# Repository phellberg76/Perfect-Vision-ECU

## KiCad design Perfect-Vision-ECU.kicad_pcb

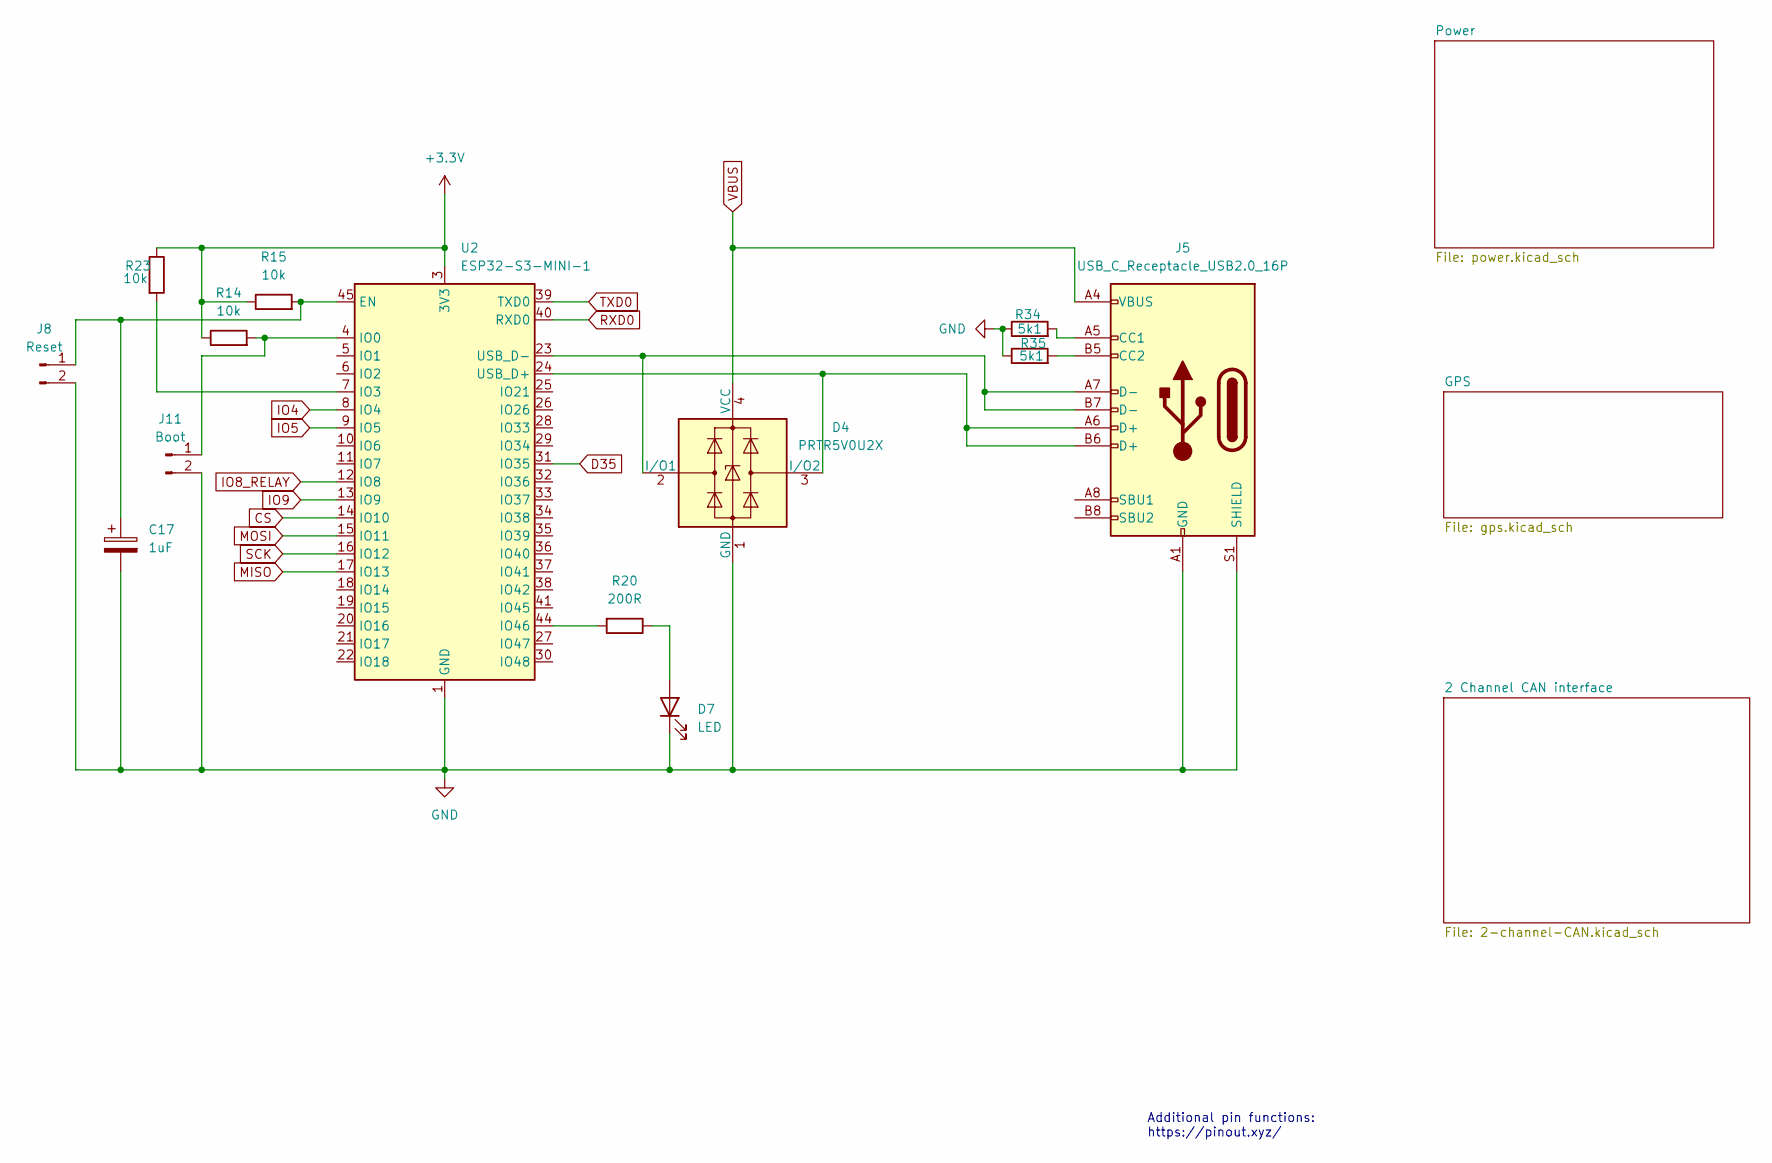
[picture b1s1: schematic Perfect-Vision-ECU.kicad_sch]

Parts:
C17: 1uF; C_0402_1005Metric
D4: PRTR5V0U2X; SOT-143
D7: LED; LED_0603_1608Metric
J5: USB_C_Receptacle_USB2.0_16P; USB_C_Receptacle_HRO_TYPE-C-31-M-12
J8: Reset; PinHeader_1x02_P2.54mm_Vertical
J11: Boot; PinHeader_1x02_P2.54mm_Vertical
R14, R15, R23: 10k; R_0402_1005Metric
R20: 200R; R_0603_1608Metric
R34, R35: 5k1; R_0402_1005Metric
U2: ESP32-S3-MINI-1; ESP32-S2-MINI-1

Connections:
+3.3V: R14.1, R15.1, R23.1, U2.3 (3V3); also elsewhere on the board
CS: U2.14 (IO10); also elsewhere on the board
D35: U2.31 (IO35); also elsewhere on the board
GND: C17.2, D4.1 (GND), D7.1 (K), J5.A1 (GND), J5.A12 (GND), J5.B1 (GND), J5.B12 (GND), J5.S1 (SHIELD), J8.2, J11.2, R34.1, R35.1, U2.1 (GND), U2.2 (GND), U2.42 (GND), U2.43 (GND), U2.46 (GND), U2.47 (GND), U2.48 (GND), U2.49 (GND), U2.50 (GND), U2.51 (GND), U2.52 (GND), U2.53 (GND), U2.54 (GND), U2.55 (GND), U2.56 (GND), U2.57 (GND), U2.58 (GND), U2.59 (GND), U2.60 (GND), U2.61 (GND), U2.62 (GND), U2.63 (GND), U2.64 (GND), U2.65 (GND); also elsewhere on the board
IO4: U2.8 (IO4); also elsewhere on the board
IO5: U2.9 (IO5); also elsewhere on the board
IO8_RELAY: U2.12 (IO8); also elsewhere on the board
IO9: U2.13 (IO9); also elsewhere on the board
MISO: U2.17 (IO13); also elsewhere on the board
MOSI: U2.15 (IO11); also elsewhere on the board
unnamed: D4.2 (I/O1), J5.A7 (D-), J5.B7 (D-), U2.23 (USB_D-)
unnamed: D4.3 (I/O2), J5.A6 (D+), J5.B6 (D+), U2.24 (USB_D+)
unnamed: D7.2 (A), R20.1
unnamed: J5.A5 (CC1), R34.2
unnamed: J5.B5 (CC2), R35.2
unnamed: C17.1, J8.1, R15.2, U2.45 (EN)
unnamed: J11.1, R14.2, U2.4 (IO0)
unnamed: R23.2, U2.7 (IO3)
unnamed: R20.2, U2.44 (IO46)
RXD0: U2.40 (RXD0); also elsewhere on the board
SCK: U2.16 (IO12); also elsewhere on the board
TXD0: U2.39 (TXD0); also elsewhere on the board
VBUS: D4.4 (VCC), J5.A4 (VBUS), J5.A9 (VBUS), J5.B4 (VBUS), J5.B9 (VBUS); also elsewhere on the board

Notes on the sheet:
Additional pin functions: https://pinout.xyz/

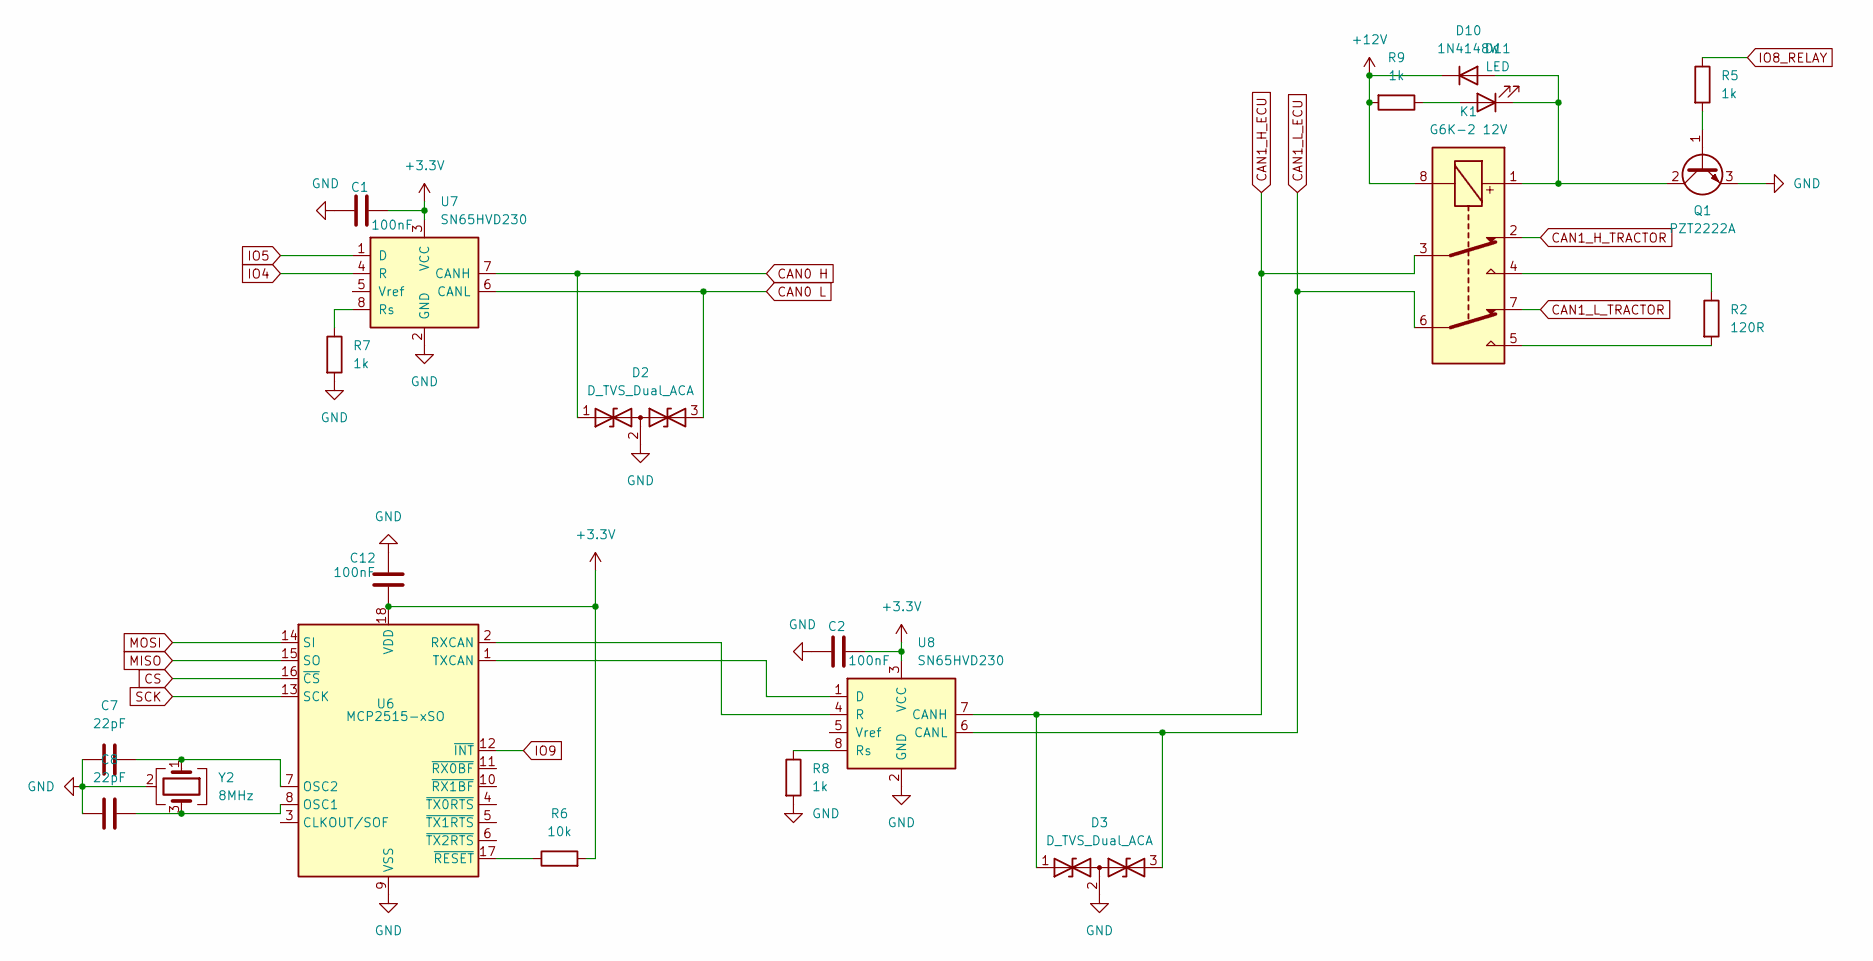
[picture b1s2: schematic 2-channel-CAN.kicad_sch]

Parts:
C1, C2, C12: 100nF; C_0402_1005Metric
C7, C8: 22pF; C_0402_1005Metric
D2, D3: D_TVS_Dual_ACA; SOT-23
D10: 1N4148W; D_SOD-123
D11: LED; LED_0603_1608Metric
K1: G6K-2 12V; Relay_DPDT_Omron_G6K-2F-Y
Q1: PZT2222A; SOT-223-3_TabPin2
R2: 120R; R_0402_1005Metric
R5, R7, R8, R9: 1k; R_0402_1005Metric
R6: 10k; R_0402_1005Metric
U6: MCP2515-xSO; SOIC-18W_7.5x11.6mm_P1.27mm
U7, U8: SN65HVD230; SOIC-8_3.9x4.9mm_P1.27mm
Y2: 8MHz; Crystal_SMD_3225-4Pin_3.2x2.5mm

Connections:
+3.3V: C1.1, C2.1, C12.2, R6.2, U6.18 (VDD), U7.3 (VCC), U8.3 (VCC); also elsewhere on the board
+12V: D10.1 (K), K1.8, R9.2; also elsewhere on the board
CAN0 H: D2.1 (A1), U7.7 (CANH); also elsewhere on the board
CAN0 L: D2.3 (A2), U7.6 (CANL); also elsewhere on the board
CAN1_H_ECU: D3.1 (A1), K1.3, U8.7 (CANH); also elsewhere on the board
CAN1_H_TRACTOR: K1.2; also elsewhere on the board
CAN1_L_ECU: D3.3 (A2), K1.6, U8.6 (CANL); also elsewhere on the board
CAN1_L_TRACTOR: K1.7; also elsewhere on the board
CS: U6.16 (~CS); also elsewhere on the board
GND: C1.2, C2.2, C7.1, C8.1, C12.1, D2.2 (common), D3.2 (common), Q1.3 (E), R7.2, R8.2, U6.9 (VSS), U7.2 (GND), U8.2 (GND), Y2.2 (G), Y2.4 (G); also elsewhere on the board
IO4: U7.4 (R); also elsewhere on the board
IO5: U7.1 (D); also elsewhere on the board
IO8_RELAY: R5.1; also elsewhere on the board
IO9: U6.12 (~INT); also elsewhere on the board
MISO: U6.15 (SO); also elsewhere on the board
MOSI: U6.14 (SI); also elsewhere on the board
unnamed: D10.2 (A), D11.1 (K), K1.1, Q1.2 (C)
unnamed: D11.2 (A), R9.1
unnamed: K1.4, R2.1
unnamed: K1.5, R2.2
unnamed: Q1.1 (B), R5.2
unnamed: C8.2, U6.8 (OSC1), Y2.3
unnamed: C7.2, U6.7 (OSC2), Y2.1
unnamed: U6.2 (RXCAN), U8.4 (R)
unnamed: U6.1 (TXCAN), U8.1 (D)
unnamed: R6.1, U6.17 (~RESET)
unnamed: R7.1, U7.8 (Rs)
unnamed: R8.1, U8.8 (Rs)
SCK: U6.13 (SCK); also elsewhere on the board

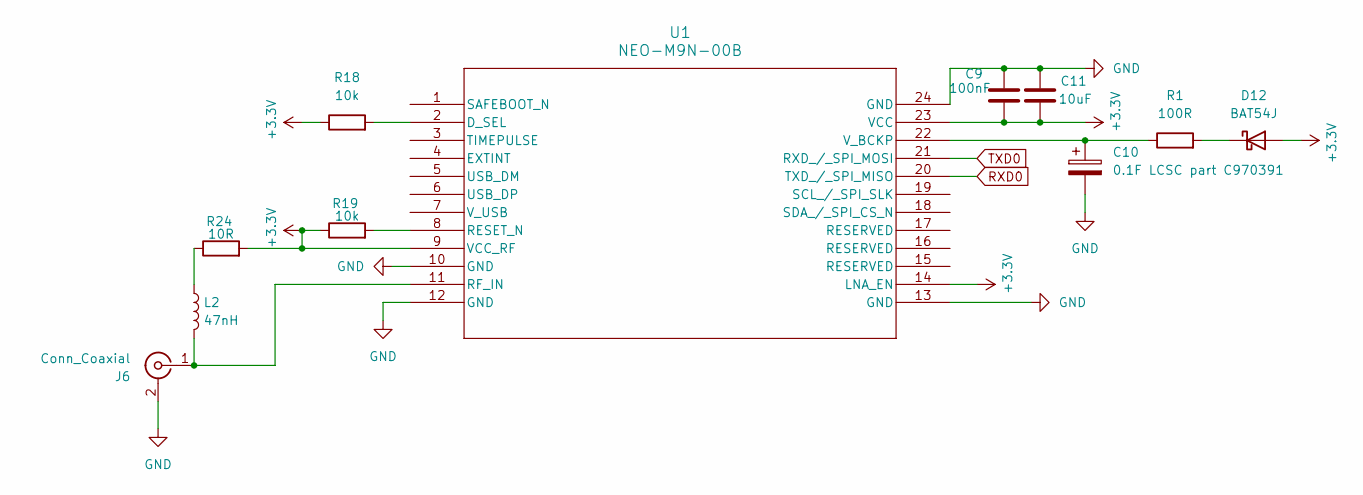
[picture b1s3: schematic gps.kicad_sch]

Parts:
C9: 100nF; C_0402_1005Metric
C10: 0.1F LCSC part C970391; CP_Radial_D8.0mm_P3.50mm
C11: 10uF; C_0805_2012Metric
D12: BAT54J; D_SOD-323F
J6: Conn_Coaxial; U.FL_Hirose_U.FL-R-SMT-1_Vertical
L2: 47nH; L_0402_1005Metric
R1: 100R; R_0402_1005Metric
R18, R19: 10k; R_0402_1005Metric
R24: 10R; R_0402_1005Metric
U1: NEO-M9N-00B; SMT_9N-00B_UBL

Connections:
+3.3V: C9.2, C11.2, D12.2 (A), R18.1, R19.1, R24.2, U1.9 (VCC_RF), U1.14 (LNA_EN), U1.23 (VCC); also elsewhere on the board
GND: C9.1, C10.2, C11.1, J6.2 (Ext), U1.10 (GND), U1.12 (GND), U1.13 (GND), U1.24 (GND); also elsewhere on the board
unnamed: D12.1 (K), R1.2
unnamed: J6.1 (In), L2.2, U1.11 (RF_IN)
unnamed: L2.1, R24.1
unnamed: R18.2, U1.2 (D_SEL)
unnamed: R19.2, U1.8 (RESET_N)
unnamed: C10.1, R1.1, U1.22 (V_BCKP)
RXD0: U1.20 (TXD_/_SPI_MISO); also elsewhere on the board
TXD0: U1.21 (RXD_/_SPI_MOSI); also elsewhere on the board

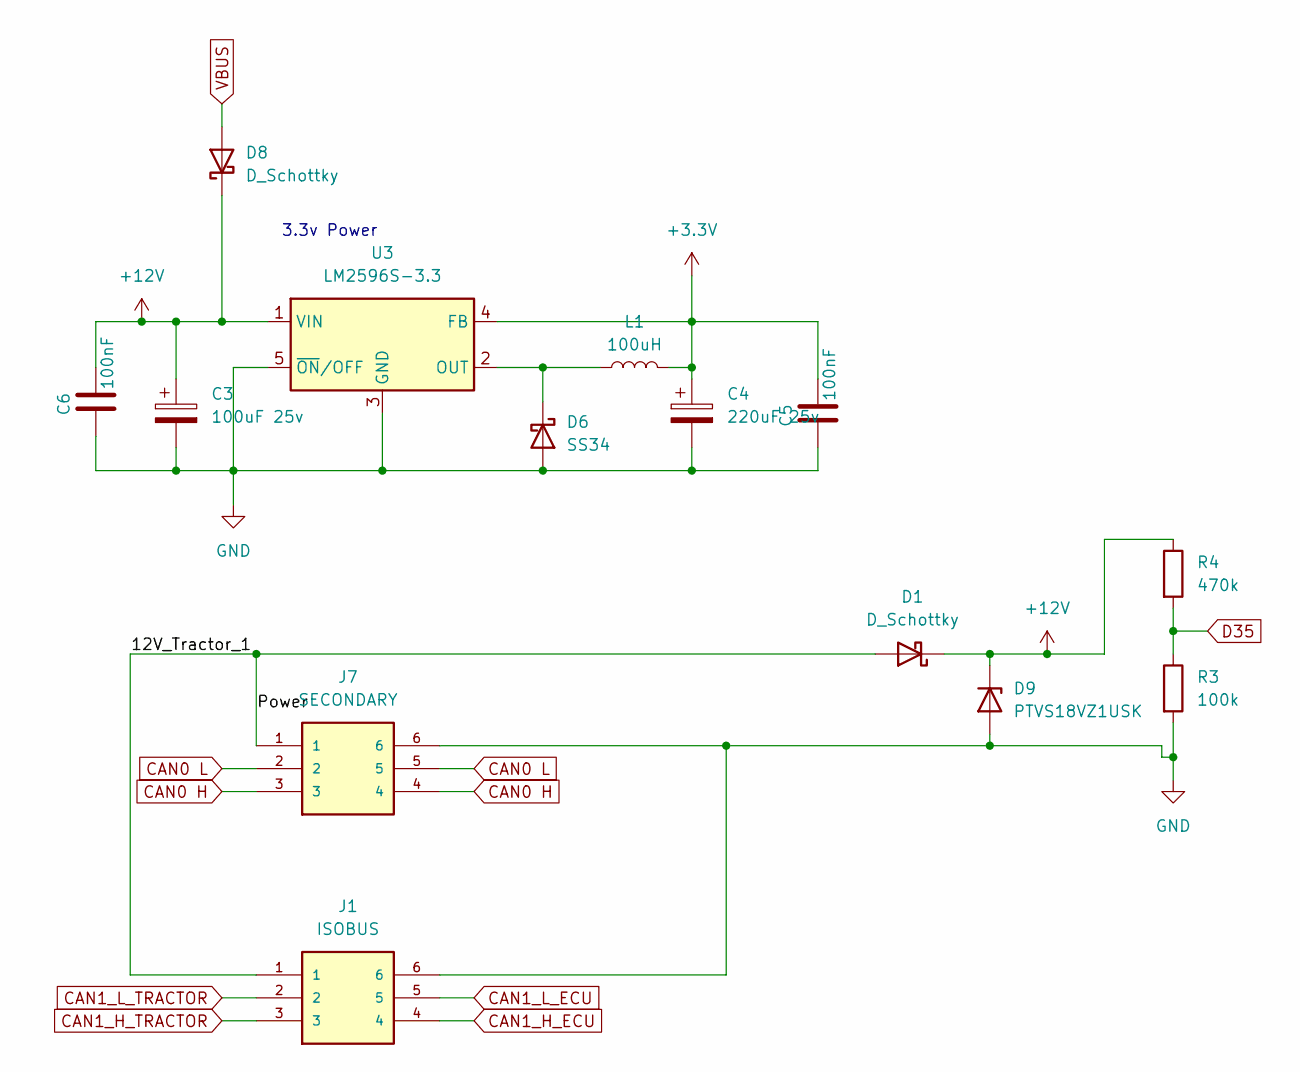
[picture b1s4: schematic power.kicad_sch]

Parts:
C3: 100uF 25v; CP_Elec_6.3x7.7
C4: 220uF 25v; CP_Elec_8x10.5
C5, C6: 100nF; C_0402_1005Metric
D1, D8: D_Schottky; D_SMC
D6: SS34; D_SMA
D9: PTVS18VZ1USK; D_SMA
J1: ISOBUS; AT04-6P-BM; PARTREV C1
J7: SECONDARY; AT04-6P-BM; PARTREV C1
L1: 100uH; L_12x12mm_H4.5mm
R3: 100k; R_0402_1005Metric
R4: 470k; R_0402_1005Metric
U3: LM2596S-3.3; TO-263-5_TabPin3

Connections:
+3.3V: C4.1, C5.1, L1.2, U3.4 (FB); also elsewhere on the board
+12V: C3.1, C6.1, D1.1 (K), D8.1 (K), D9.1 (K), R4.1, U3.1 (VIN); also elsewhere on the board
/Power/12V_Tractor_1: D1.2 (A), J1.1, J7.1
CAN0 H: J7.3, J7.4; also elsewhere on the board
CAN0 L: J7.2, J7.5; also elsewhere on the board
CAN1_H_ECU: J1.4; also elsewhere on the board
CAN1_H_TRACTOR: J1.3; also elsewhere on the board
CAN1_L_ECU: J1.5; also elsewhere on the board
CAN1_L_TRACTOR: J1.2; also elsewhere on the board
D35: R3.1, R4.2; also elsewhere on the board
GND: C3.2, C4.2, C5.2, C6.2, D6.2 (A), D9.2 (A), J1.6, J7.6, R3.2, U3.3 (GND), U3.5 (~ON/OFF); also elsewhere on the board
unnamed: D6.1 (K), L1.1, U3.2 (OUT)
VBUS: D8.2 (A); also elsewhere on the board

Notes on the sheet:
3.3v Power

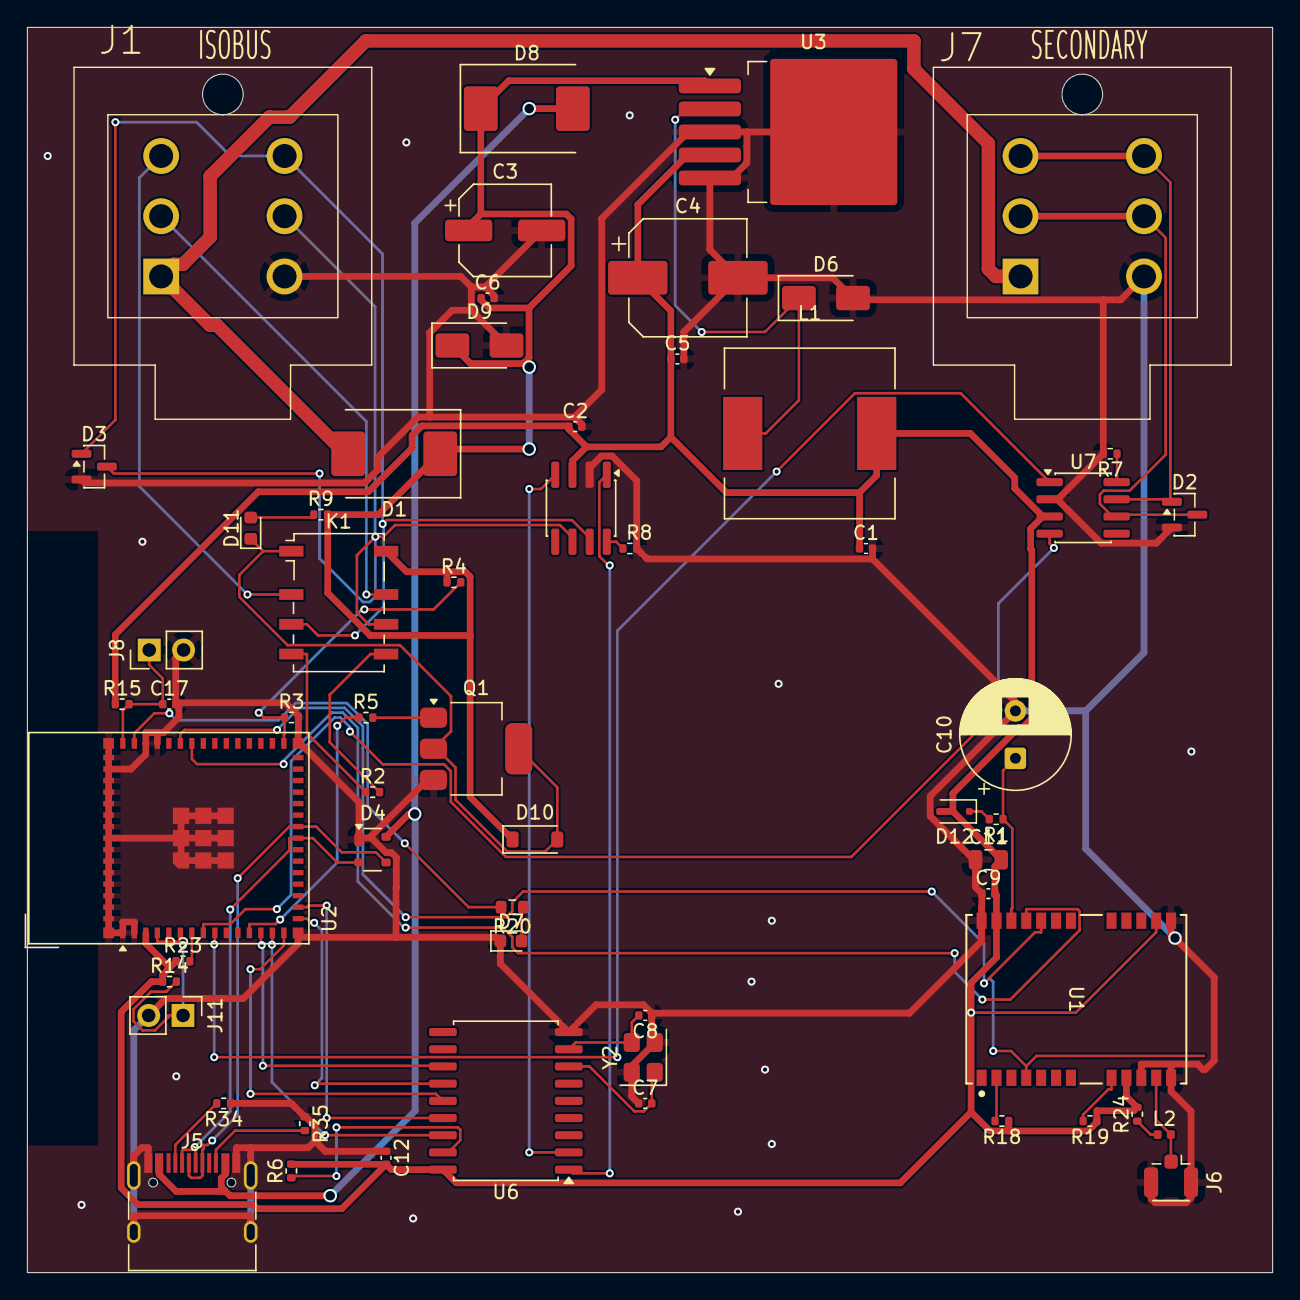
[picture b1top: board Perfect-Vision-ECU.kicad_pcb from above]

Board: 2 copper layers, 92.0 x 92.0 mm, 59 parts (0 on the bottom side), 50 nets.

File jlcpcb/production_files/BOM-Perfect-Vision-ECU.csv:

Comment,Designator,Footprint,LCSC,Quantity
100R,R1,R_0402_1005Metric,C25076,1
100k,R3,R_0402_1005Metric,C25741,1
100nF,"C1,C12,C2,C5,C6,C9",C_0402_1005Metric,C1525,6
100uF 25v,C3,CP_Elec_6.3x7.7,C72477,1
100uH,L1,L_12x12mm_H4.5mm,C504036,1
10R,R24,R_0402_1005Metric,C25077,1
10k,"R14,R15,R23",R_0402_1005Metric,C25744,3
10k,"R18,R19,R6",R_0402_1005Metric,C2906861,3
10uF,C11,C_0805_2012Metric,C15850,1
120R,R2,R_0402_1005Metric,C25079,1
1N4148W,D10,D_SOD-123,C81598,1
1k,"R5,R7,R8,R9",R_0402_1005Metric,C11702,4
1uF,C17,C_0402_1005Metric,C52923,1
200R,R20,R_0603_1608Metric,C8218,1
220uF 25v,C4,CP_Elec_8x10.5,C3353,1
22pF,"C7,C8",C_0402_1005Metric,C1555,2
470k,R4,R_0402_1005Metric,C25790,1
47nH,L2,L_0402_1005Metric,C27151,1
5k1,"R34,R35",R_0402_1005Metric,C22356228,2
8MHz,Y2,Crystal_SMD_3225-4Pin_3.2x2.5mm,C2682774,1
BAT54J,D12,D_SOD-323F,C358488,1
Conn_Coaxial,J6,U.FL_Hirose_U.FL-R-SMT-1_Vertical,C88374,1
D_Schottky,D8,D_SMC,C13763,1
D_Schottky,D1,D_SMC,C18199210,1
D_TVS_Dual_ACA,"D2,D3",SOT-23,C284078,2
ESP32-S3-MINI-1,U2,ESP32-S2-MINI-1,C2913206,1
G6K-2 12V,K1,Relay_DPDT_Omron_G6K-2F-Y,C397194,1
LED,"D11,D7",LED_0603_1608Metric,C2286,2
LM2596S-3.3,U3,TO-263-5_TabPin3,C347420,1
MCP2515-xSO,U6,SOIC-18W_7.5x11.6mm_P1.27mm,C153782,1
NEO-M9N-00B,U1,SMT_9N-00B_UBL,C5119087,1
PRTR5V0U2X,D4,SOT-143,C5158049,1
PTVS18VZ1USK,D9,D_SMA,C134965,1
PZT2222A,Q1,SOT-223-3_TabPin2,C115272,1
SN65HVD230,"U7,U8",SOIC-8_3.9x4.9mm_P1.27mm,C12084,2
SS34,D6,D_SMA,C8678,1
USB_C_Receptacle_USB2.0_16P,J5,USB_C_Receptacle_HRO_TYPE-C-31-M-12,C165948,1

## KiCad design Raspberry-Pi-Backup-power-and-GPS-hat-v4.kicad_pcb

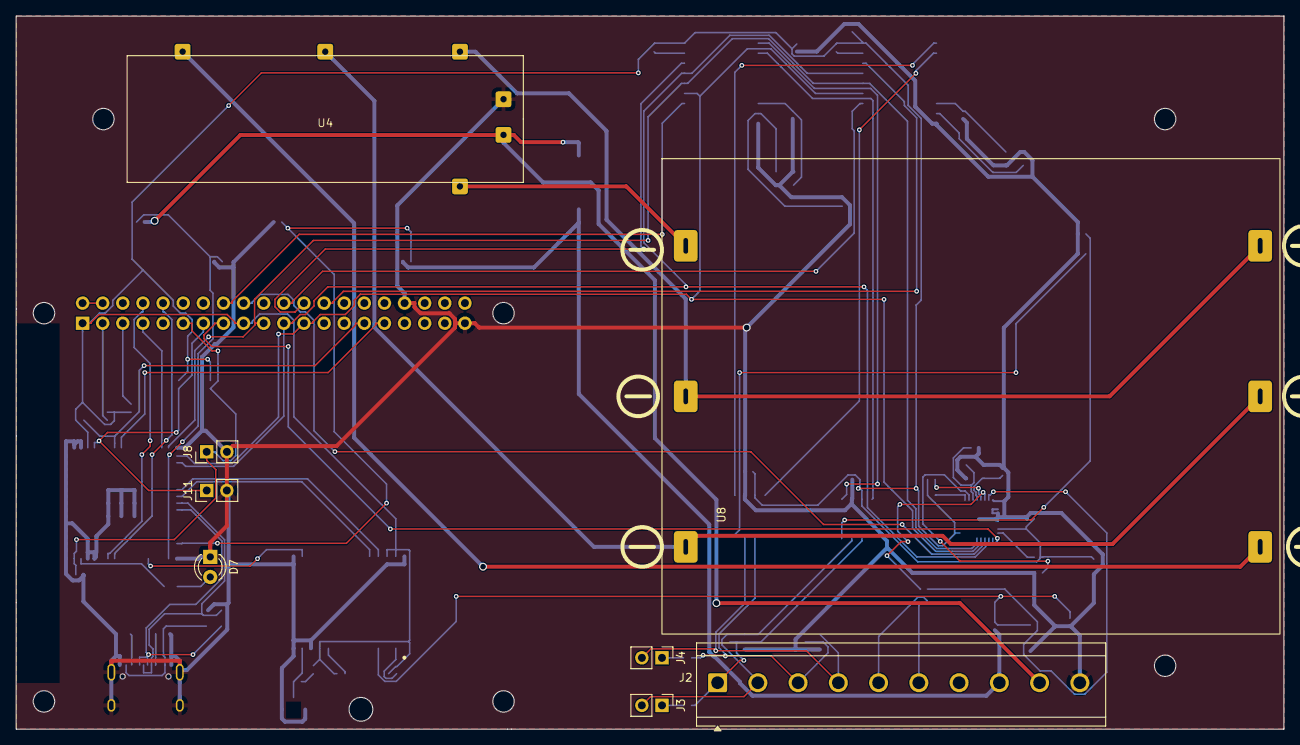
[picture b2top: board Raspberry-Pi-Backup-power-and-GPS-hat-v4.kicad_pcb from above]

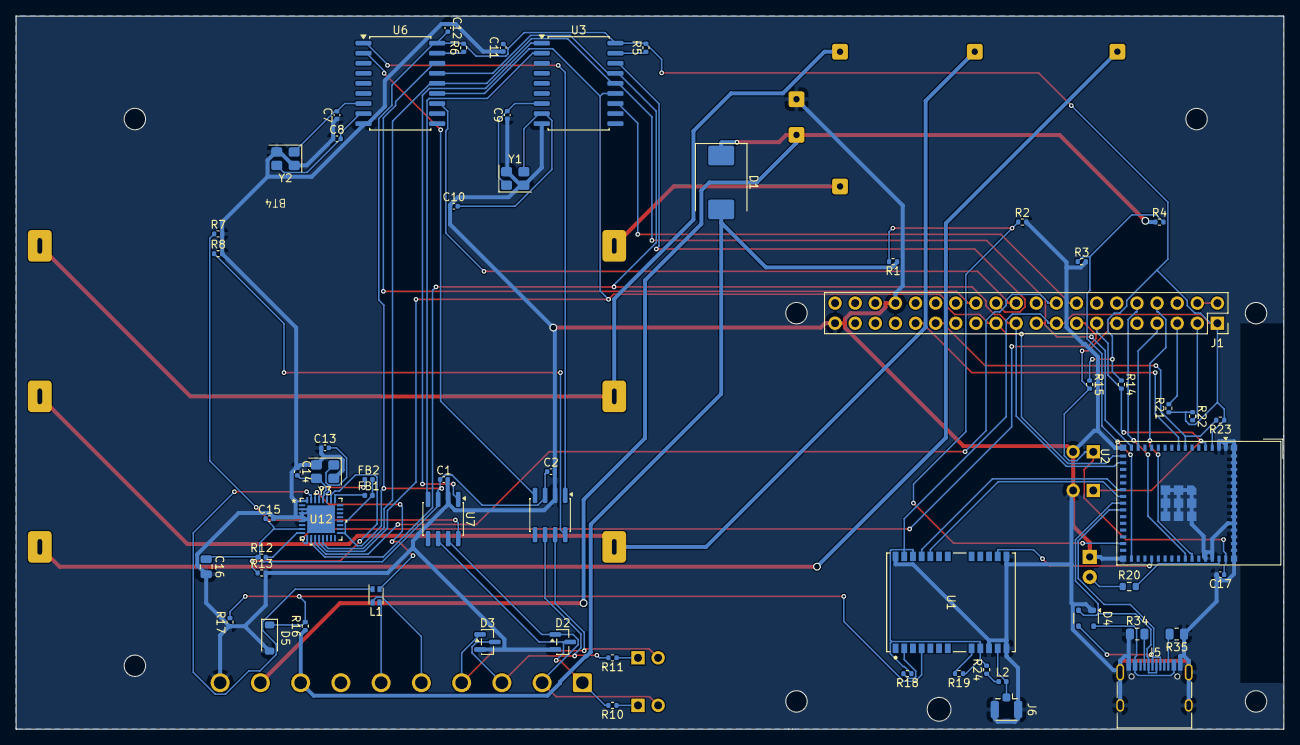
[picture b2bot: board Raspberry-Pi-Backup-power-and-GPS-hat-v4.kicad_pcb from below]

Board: 2 copper layers, 160.0 x 90.0 mm, 75 parts (60 on the bottom side), 72 nets.

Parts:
BT4: battery_3S; 18650 Battery Holder 3S RoboFactory
C1, C2, C11, C12, C15: 100nF; C_0402_1005Metric
C7, C8, C9, C10: 22pF; C_0402_1005Metric
C13, C14: 15pF; C_0402_1005Metric
C16: 10uF; C_0805_2012Metric
C17: 1uF; C_0402_1005Metric
D1: D_Schottky; D_SMC
D2, D3: D_TVS_Dual_ACA; SOT-23
D4: PRTR5V0U2X; SOT-143
D5: 3.3v; D_SOD-123
D7: LED; LED_D3.0mm
FB1, FB2: FerriteBead; L_0402_1005Metric
J1: GPIO; PinSocket_2x20_P2.54mm_Vertical
J2: TerminalBlock_CUI_TB007-508-10_1x10_P5.08mm_Horizontal
J3, J4: Conn_01x02_Pin; PinHeader_1x02_P2.54mm_Vertical
J5: USB_C_Receptacle_USB2.0_16P; USB_C_Receptacle_HRO_TYPE-C-31-M-12
J6: Conn_Coaxial; U.FL_Hirose_U.FL-R-SMT-1_Vertical
J8: Reset; PinHeader_1x02_P2.54mm_Vertical
J11: Boot; PinHeader_1x02_P2.54mm_Vertical
L1: Choke; L_CommonModeChoke_Coilcraft_0805USB
L2: 47nH; L_0402_1005Metric
MH1, MH2, MH3, MH4, MH5, MH6, MH7: MountingHole_2.7mm_M2.5
R1, R4: 470k; R_0402_1005Metric
R2, R3, R17: 100k; R_0402_1005Metric
R5, R6, R12, R14, R15, R16, R18, R19, R23: 10k; R_0402_1005Metric
R7, R8: 1k; R_0402_1005Metric
R10, R11: 120R; R_0402_1005Metric
R13: 12.4k 1%; R_0402_1005Metric
R20: 200R; R_0603_1608Metric
R21, R22: 4k7; R_0402_1005Metric
R24: 10R; R_0402_1005Metric
R34, R35: 5k1; R_0805_2012Metric
U1: NEO-M9N-00B; SMT_9N-00B_UBL
U2: ESP32-S3-MINI-1; ESP32-S2-MINI-1
U3, U6: MCP2515-xSO; SOIC-18W_7.5x11.6mm_P1.27mm
U4: BMS-3S-10
U7, U8: SN65HVD230; SOIC-8_3.9x4.9mm_P1.27mm
U12: LAN8651B1-E/LMX; VQFN32_LMX_MCH
Y1, Y2: 8MHz; Crystal_SMD_3225-4Pin_3.2x2.5mm
Y3: 25MHz; Crystal_SMD_3225-4Pin_3.2x2.5mm

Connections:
+3.3V: C1.1, C2.1, C11.2, C12.2, C15.1, C16.1, FB1.2, FB2.2, J1.1, J1.17, R5.2, R6.2, R12.1, R14.1, R15.1, R18.1, R19.1, R21.1, R22.1, R23.1, R24.2, U1.9 (VCC_RF), U1.22 (V_BCKP), U1.23 (VCC), U2.3 (3V3), U3.18 (VDD), U6.18 (VDD), U7.3 (VCC), U8.3 (VCC), U12.7 (VDDP), U12.17 (VDDP)
+5V: J1.2, J1.4
/Power B1: BT4.4 (-), BT4.5 (+), U4.3 (B1)
/Power B2: BT4.2 (-), BT4.3 (+), U4.2 (B2)
/Power B3: BT4.1 (+), U4.1 (B3(+))
/Power B-: BT4.6 (-), U4.4 (B-)
/Power Li+: D1.1 (K), J2.9, R4.1, U4.6 (P+)
CAN0 H: D2.1 (A1), J2.2, J3.2, U7.7 (CANH)
CAN0 L: D2.3 (A2), J2.1, R10.2, U7.6 (CANL)
CAN1 H: D3.1 (A1), J2.4, J4.2, U8.7 (CANH)
CAN1 L: D3.3 (A2), J2.3, R11.2, U8.6 (CANL)
CE0: J1.24, U3.16 (~CS)
CE1: J1.26, U6.16 (~CS)
D34: R1.2, R2.1, U2.29 (IO34)
D35: R3.1, R4.2, U2.31 (IO35)
GND: C1.2, C2.2, C7.1, C8.1, C9.1, C10.1, C11.1, C12.1, C13.1, C14.1, C15.2, C16.2, C17.2, D2.2 (common), D3.2 (common), D4.1 (GND), D5.2 (A), D7.1 (K), J1.34, J1.39, J2.10, J5.A1 (GND), J5.A12 (GND), J5.B1 (GND), J5.B12 (GND), J5.S1 (SHIELD), J6.2 (Ext), J8.2, J11.2, R2.2, R3.2, R7.2, R8.2, R13.2, R17.1, R34.1, R35.1, U1.10 (GND), U1.12 (GND), U1.13 (GND), U1.24 (GND), U2.1 (GND), U2.2 (GND), U2.42 (GND), U2.43 (GND), U2.46 (GND), U2.47 (GND), U2.48 (GND), U2.49 (GND), U2.50 (GND), U2.51 (GND), U2.52 (GND), U2.53 (GND), U2.54 (GND), U2.55 (GND), U2.56 (GND), U2.57 (GND), U2.58 (GND), U2.59 (GND), U2.60 (GND), U2.61 (GND), U2.62 (GND), U2.63 (GND), U2.64 (GND), U2.65 (GND), U3.9 (VSS), U4.5 (P-), U6.9 (VSS), U7.2 (GND), U8.2 (GND), U12.2 (VSS), U12.3 (VSS), U12.4 (TEST), U12.5 (VSS), U12.32 (WAKE_IN), U12.33 (VSS), Y1.2 (G), Y1.4 (G), Y2.2 (G), Y2.4 (G), Y3.2 (G), Y3.4 (G)
GPIO4_CS: J1.7, U2.14 (IO10)
GPIO5: J1.29, R23.2, U2.7 (IO3)
GPIO6: J1.31, U2.8 (IO4)
GPIO17: C17.1, J1.11, J8.1, R15.2, U2.45 (EN)
GPIO22: J1.15, U12.9 (IRQ_N)
GPIO23: J1.16, U3.12 (~INT)
GPIO24: J1.18, U12.11 (CS_N)
GPIO25: J1.22, U6.12 (~INT)
GPIO27: J1.13, J11.1, R14.2, U2.4 (IO0)
LNA_EN: U1.14 (LNA_EN), U2.34 (IO38)
MISO: J1.21, U2.17 (IO13), U3.15 (SO), U6.15 (SO), U12.10 (SDO)
MOSI: J1.19, U2.15 (IO11), U3.14 (SI), U6.14 (SI), U12.13 (SDI)
unnamed: D4.2 (I/O1), J5.A7 (D-), J5.B7 (D-), U2.23 (USB_D-)
unnamed: D4.3 (I/O2), J5.A6 (D+), J5.B6 (D+), U2.24 (USB_D+)
unnamed: D4.4 (VCC), J5.A4 (VBUS), J5.A9 (VBUS), J5.B4 (VBUS), J5.B9 (VBUS)
unnamed: D5.1 (K), R16.2, R17.2, U1.4 (EXTINT)
unnamed: D7.2 (A), R20.1
unnamed: J3.1, R10.1
unnamed: J4.1, R11.1
unnamed: J5.A5 (CC1), R34.2
unnamed: J5.B5 (CC2), R35.2
unnamed: J6.1 (In), L2.2, U1.11 (RF_IN)
unnamed: L2.1, R24.1
unnamed: R18.2, U1.2 (D_SEL)
unnamed: R19.2, U1.8 (RESET_N)
unnamed: R20.2, U2.44 (IO46)
unnamed: C10.2, U3.8 (OSC1), Y1.3
unnamed: C9.2, U3.7 (OSC2), Y1.1
unnamed: U3.2 (RXCAN), U7.4 (R)
unnamed: U3.1 (TXCAN), U7.1 (D)
unnamed: R5.1, U3.17 (~RESET)
unnamed: C8.2, U6.8 (OSC1), Y2.3
unnamed: C7.2, U6.7 (OSC2), Y2.1
unnamed: U6.2 (RXCAN), U8.4 (R)
unnamed: U6.1 (TXCAN), U8.1 (D)
unnamed: R6.1, U6.17 (~RESET)
unnamed: R7.1, U7.8 (Rs)
unnamed: R8.1, U8.8 (Rs)
unnamed: R13.1, U12.26 (RBIAS)
unnamed: R12.2, U12.8 (RESET_N)
unnamed: L1.1, U12.31 (TRXN)
unnamed: L1.4, U12.30 (TRXP)
unnamed: FB2.1, U12.29 (VDDA)
unnamed: FB1.1, U12.25 (VDDAU)
unnamed: C13.2, U12.27 (XTI), Y3.1
unnamed: C14.2, U12.28 (XTO), Y3.3
RXD0: J1.10, U2.39 (TXD0)
RXD1: U1.20 (TXD_/_SPI_MISO), U2.22 (IO18)
SCK: J1.23, U2.16 (IO12), U3.13 (SCK), U6.13 (SCK), U12.12 (SCLK)
SCL1: J1.5, R21.2
SDA1: J1.3, R22.2
T1N: J2.5, L1.2
T1P: J2.6, L1.3
TXD0: J1.8, U2.40 (RXD0)
TXD1: U1.21 (RXD_/_SPI_MOSI), U2.21 (IO17)
V_TRACTOR: D1.2 (A), J2.8, R1.1, R16.1

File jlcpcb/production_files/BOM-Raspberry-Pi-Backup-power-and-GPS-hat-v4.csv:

Comment,Designator,Footprint,LCSC,Quantity
100k,"R17,R2,R3",R_0402_1005Metric,C25741,3
100nF,"C1,C11,C12,C15,C2",C_0402_1005Metric,C1525,5
10R,R24,R_0402_1005Metric,C25077,1
10k,"R12,R14,R15,R16,R18,R19,R23,R5,R6",R_0402_1005Metric,C2906861,9
10uF,C16,C_0805_2012Metric,C15850,1
12.4k 1%,R13,R_0402_1005Metric,C11692,1
120R,"R10,R11",R_0402_1005Metric,C25079,2
15pF,"C13,C14",C_0402_1005Metric,C1548,2
1k,"R7,R8",R_0402_1005Metric,C11702,2
1uF,C17,C_0402_1005Metric,C52923,1
200R,R20,R_0603_1608Metric,C8218,1
22pF,"C10,C7,C8,C9",C_0402_1005Metric,C1555,4
25MHz,Y3,Crystal_SMD_3225-4Pin_3.2x2.5mm,C9006,1
3.3v,D5,D_SOD-123,C19077396,1
470k,"R1,R4",R_0402_1005Metric,C137976,2
47nH,L2,L_0402_1005Metric,C27151,1
4k7,"R21,R22",R_0402_1005Metric,C105870,2
5k1,"R34,R35",R_0805_2012Metric,C115309,2
8MHz,"Y1,Y2",Crystal_SMD_3225-4Pin_3.2x2.5mm,C115962,2
Choke,L1,L_CommonModeChoke_Coilcraft_0805USB,C1046,1
Conn_Coaxial,J6,U.FL_Hirose_U.FL-R-SMT-1_Vertical,C88374,1
D_TVS_Dual_ACA,"D2,D3",SOT-23,C284078,2
ESP32-S3-MINI-1,U2,ESP32-S2-MINI-1,C2913206,1
FerriteBead,"FB1,FB2",L_0402_1005Metric,C141722,2
MCP2515-xSO,"U3,U6",SOIC-18W_7.5x11.6mm_P1.27mm,C153782,2
NEO-M9N-00B,U1,SMT_9N-00B_UBL,C5119087,1
PRTR5V0U2X,D4,SOT-143,C5158049,1
SN65HVD230,"U7,U8",SOIC-8_3.9x4.9mm_P1.27mm,C12084,2
USB_C_Receptacle_USB2.0_16P,J5,USB_C_Receptacle_HRO_TYPE-C-31-M-12,C165948,1
